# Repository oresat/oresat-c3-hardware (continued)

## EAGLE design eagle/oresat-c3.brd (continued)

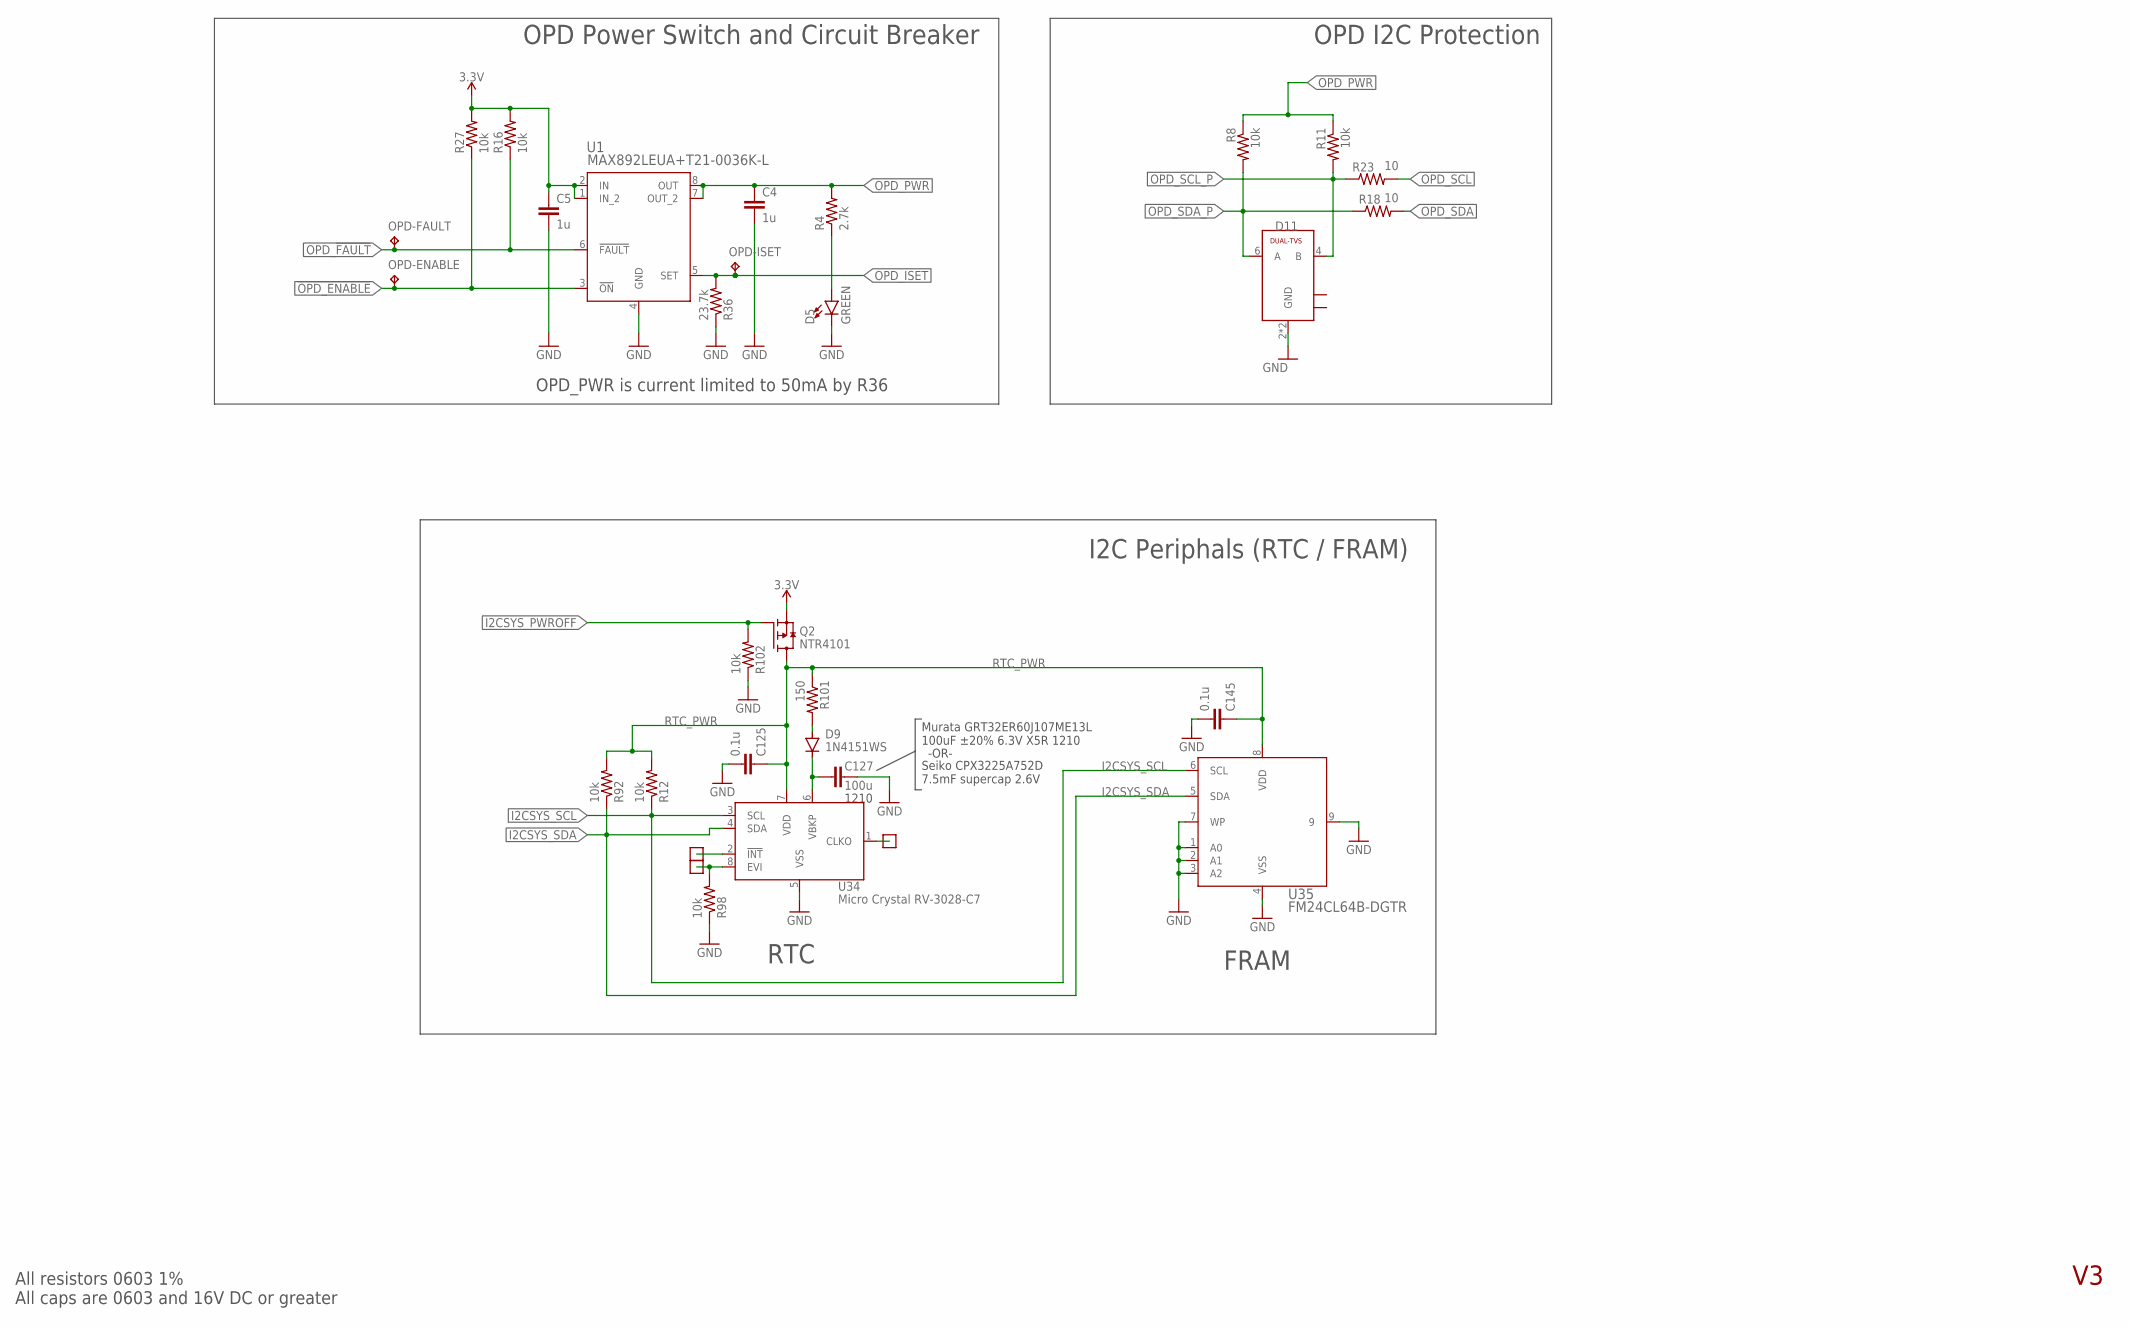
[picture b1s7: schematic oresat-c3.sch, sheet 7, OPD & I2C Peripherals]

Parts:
C4, C5: 1u; .0603-C-NOSILK
C125, C145: 0.1u; .0603-C-NOSILK
C127: 100u; C1210K
D5: GREEN; LED-0603; MANUFACTURER_PART_NUMBER 150060VS55040; DIGI-KEY_PART_NUMBER 732-12017-1-ND
D9: 1N4151WS; SOD323-R
D11: SN65220; SOT23-6; MANUFACTURER_PART_NUMBER SN65220DBVRG4
OPD-ENABLE: TEST-POINT-LARGE; 1X01
OPD-FAULT: TEST-POINT-LARGE; 1X01
OPD-ISET: TEST-POINT-LARGE; 1X01
Q2: NTR4101; SOT23-3
R4: 2.7k; .0603-C-NOSILK
R8, R11, R12, R16, R27, R92, R98, R102: 10k; .0603-C-NOSILK
R18, R23: 10; .0603-C-NOSILK
R36: 23.7k; .0603-C-NOSILK
R101: 150; .0603-C-NOSILK
TP16, TP23, TP24: TEST-POINT-LARGE-SQUARE; 1X01
U1: MAX892LEUA+T21-0036K-L; 21-0036K-L; MOUSER_PART_NUMBER 700-MAX892LEUAT
U34: Micro Crystal RV-3028-C7; RV3028C732768KHZ1PPMTAQC
U35: FM24CL64B-DGTR; TDFN-8

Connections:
3.3V: C5.1, Q2.2 (S), R16.2, R27.2, U1.1 (IN_2), U1.2 (IN); also elsewhere on the board
!OPD_ENABLE: OPD-ENABLE.1, R27.1, U1.3 (!ON); also elsewhere on the board
GND: C4.2, C5.2, C125.2, C127.2, C145.2, D5.C, D11.2 (GND), D11.5 (GND), R36.1, R98.1, R102.1, U1.4 (GND), U34.5 (VSS), U35.1 (A0), U35.2 (A1), U35.3 (A2), U35.4 (VSS), U35.7 (WP), U35.9; also elsewhere on the board
I2CSYS_PWROFF: Q2.1 (G), R102.2; also elsewhere on the board
I2CSYS_SCL: R12.1, U34.3 (SCL), U35.6 (SCL); also elsewhere on the board
I2CSYS_SDA: R92.1, U34.4 (SDA), U35.5 (SDA); also elsewhere on the board
unnamed: R98.2, TP23.1, U34.8 (EVI)
unnamed: TP16.1, U34.2 (!INT)
unnamed: TP24.1, U34.1 (CLKO)
unnamed: D9.A, R101.2
unnamed: C127.1, D9.C, U34.6 (VBKP)
unnamed: D5.A, R4.1
OPD_!FAULT: OPD-FAULT.1, R16.1, U1.6 (!FAULT); also elsewhere on the board
OPD_ISET: OPD-ISET.1, R36.2, U1.5 (SET); also elsewhere on the board
OPD_PWR: C4.1, R4.2, R8.1, R11.1, U1.7 (OUT_2), U1.8 (OUT); also elsewhere on the board
OPD_SCL: R23.2; also elsewhere on the board
OPD_SCL_P: D11.4 (B), R11.2, R23.1; also elsewhere on the board
OPD_SDA: R18.2; also elsewhere on the board
OPD_SDA_P: D11.6 (A), R8.2, R18.1; also elsewhere on the board
RTC_PWR: C125.1, C145.1, Q2.3 (D), R12.2, R92.2, R101.1, U34.7 (VDD), U35.8 (VDD)

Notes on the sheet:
All resistors 0603 1% All caps are 0603 and 16V DC or greater
OPD Power Switch and Circuit Breaker
OPD_PWR is current limited to 50mA by R36
1210
Murata GRT32ER60J107ME13L 100uF ±20% 6.3V X5R 1210
Seiko CPX3225A752D 7.5mF supercap 2.6V
-OR-
RTC
FRAM
I2C Periphals (RTC / FRAM)
OPD I2C Protection

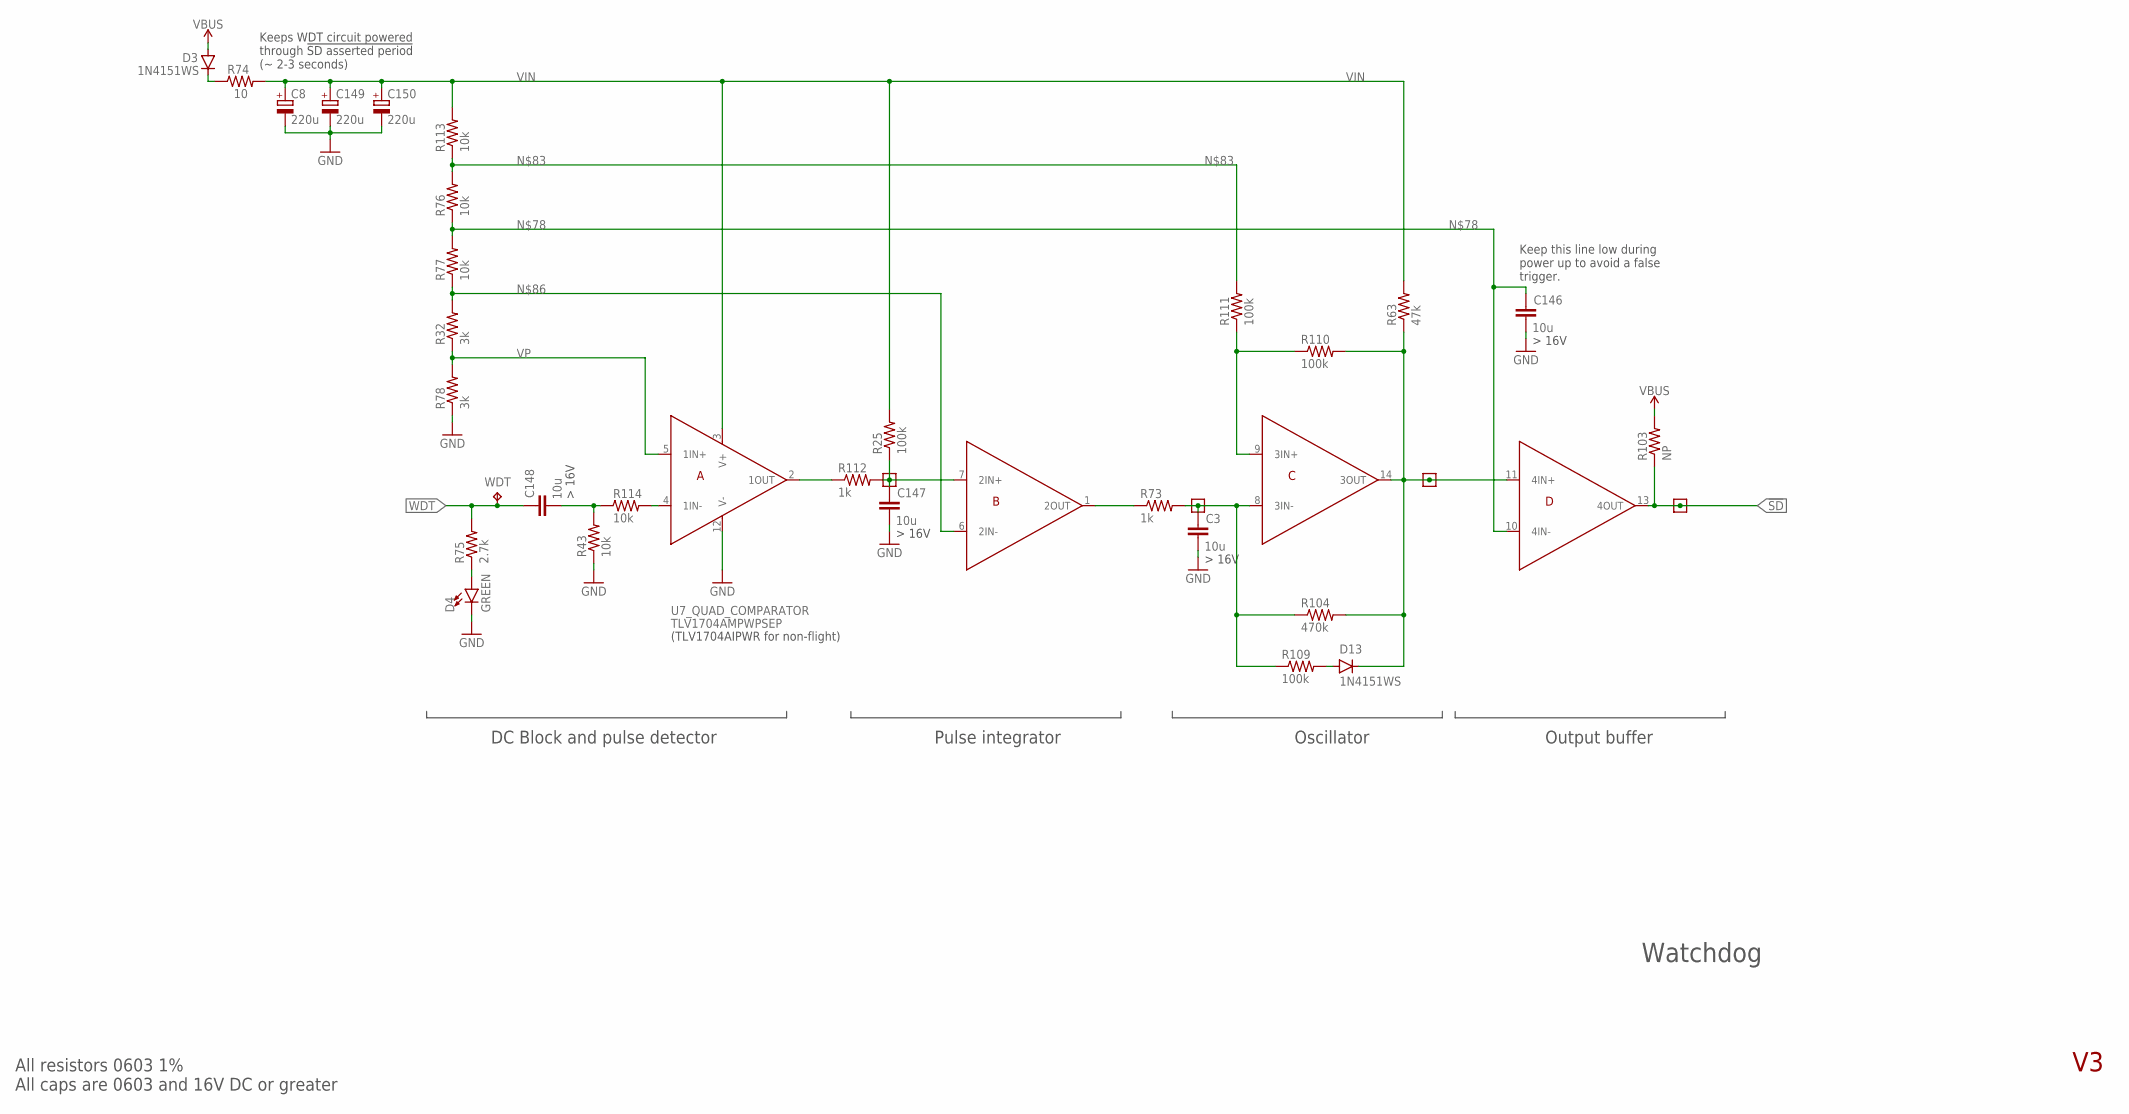
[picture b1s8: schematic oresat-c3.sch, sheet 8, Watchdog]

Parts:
C3, C146, C147, C148: 10u; .0603-C-NOSILK
C8, C149, C150: 220u; D/7343-31R
D3, D13: 1N4151WS; SOD323-R
D4: GREEN; LED-0603; MANUFACTURER_PART_NUMBER 150060VS55040; DIGI-KEY_PART_NUMBER 732-12017-1-ND
R25, R109, R110, R111: 100k; .0603-C-NOSILK
R32, R78: 3k; .0603-C-NOSILK
R43, R76, R77, R113, R114: 10k; .0603-C-NOSILK
R63: 47k; .0603-C-NOSILK
R73, R112: 1k; .0603-C-NOSILK
R74: 10; 1206-C
R75: 2.7k; .0603-C-NOSILK
R103: NP; .0603-C-NOSILK
R104: 470k; .0603-C-NOSILK
TP15, TP25, TP26, TP27: TEST-POINT-LARGE-SQUARE; 1X01
U7: TLV1704AMPWPSEP; SOP65P640X120-14N
WDT: TEST-POINT-LARGE; 1X01

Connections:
!SD: R103.1, TP15.1, U7.13 (4OUT); also elsewhere on the board
GND: C3.2, C8.-, C146.2, C147.2, C149.-, C150.-, D4.C, R43.1, R78.1, U7.12 (V-); also elsewhere on the board
unnamed: R110.1, R111.1, U7.9 (3IN+)
unnamed: D3.C, R74.1
unnamed: D4.A, R75.1
unnamed: D13.C, R63.1, R104.2, R110.2, TP25.1, U7.11 (4IN+), U7.14 (3OUT)
unnamed: R114.2, U7.4 (1IN-)
unnamed: D13.A, R109.2
unnamed: C146.1, R76.1, R77.2, U7.10 (4IN-)
unnamed: C148.2, R43.2, R114.1
unnamed: R73.1, U7.1 (2OUT)
unnamed: C147.1, R25.1, R112.2, TP27.1, U7.7 (2IN+)
unnamed: R76.2, R111.2, R113.1
unnamed: R112.1, U7.2 (1OUT)
unnamed: R32.2, R77.1, U7.6 (2IN-)
VBUS: D3.A, R103.2; also elsewhere on the board
VIN: C8.+, C149.+, C150.+, R25.2, R63.2, R74.2, R113.2, U7.3 (V+)
VP: R32.1, R78.2, U7.5 (1IN+)
VT: C3.1, R73.2, R104.1, R109.1, TP26.1, U7.8 (3IN-)
WDT: C148.1, R75.2, WDT.1; also elsewhere on the board

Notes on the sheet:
Watchdog
(TLV1704AIPWR for non-flight)
All resistors 0603 1% All caps are 0603 and 16V DC or greater
DC Block and pulse detector
Pulse integrator
Oscillator
Output buffer
Keep this line low during power up to avoid a false trigger.
Keeps WDT circuit powered through !SD asserted period (~ 2-3 seconds)

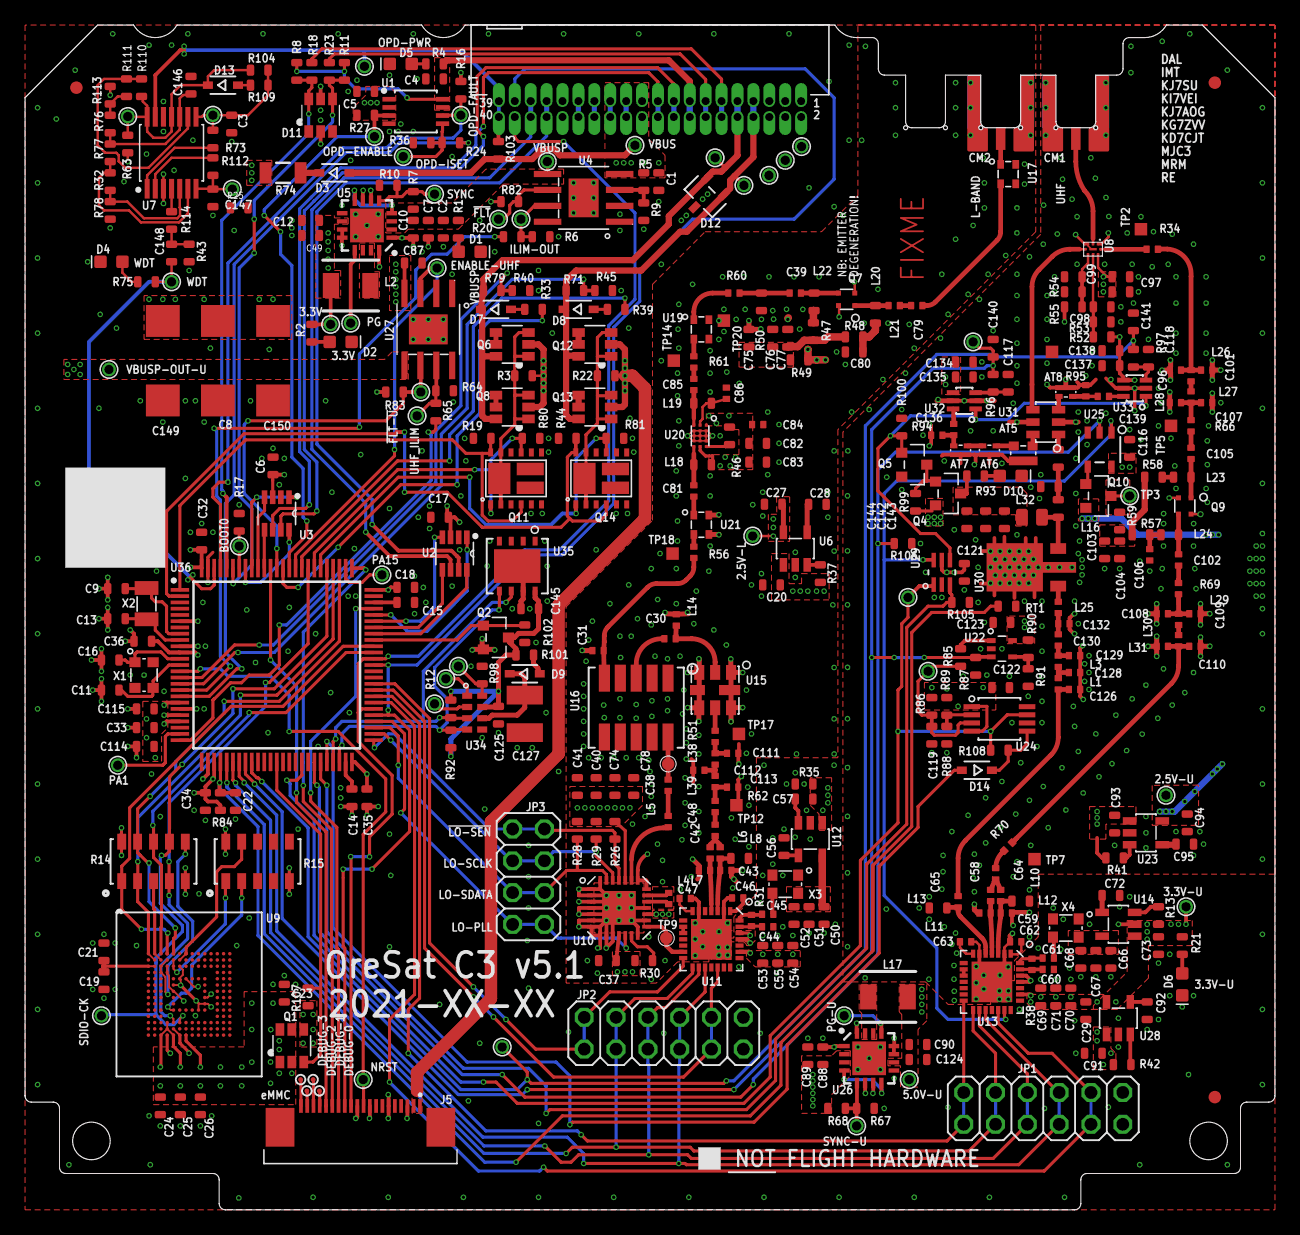
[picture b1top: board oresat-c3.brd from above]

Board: 4 copper layers, 99.8 x 94.6 mm, 441 parts (0 on the bottom side), 262 nets.

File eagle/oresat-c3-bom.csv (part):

"Part";"Value";"Device";"Package";"Description";"BOM";"DESCRIPTION";"DIGI-KEY_PART_NUMBER";"DIS";"DISTRIBUTOR";"DPN";"HEIGHT";"INVENTORY";"LABEL";"MANUFACTURER";"MANUFACTURER_NAME";"MANUFACTURER_PART_NUMBER";"MFR";"MOUSER_PART_#";"MOUSER_PART_NUMBER";"MOUSER_PRICE-STOCK";"MPN";"POPULARITY";"PROD_ID";"RS_PART_NUMBER";"RS_PRICE-STOCK";"SPICEPREFIX";"VALUE";"VDC";"VENDOR";
"!FLT";"TEST-POINT-LARGE";"TEST-POINT-LARGE";"1X01";"";"";"";"";"";"";"";"";"";"";"";"";"";"";"";"";"";"";"";"";"";"";"";"";"";"";
"!FLT-U";"TEST-POINT-LARGE";"TEST-POINT-LARGE";"1X01";"";"";"";"";"";"";"";"";"";"";"";"";"";"";"";"";"";"";"";"";"";"";"";"";"";"";
"2.5V-L";"TEST-POINT-LARGE";"TEST-POINT-LARGE";"1X01";"";"";"";"";"";"";"";"";"";"";"";"";"";"";"";"";"";"";"";"";"";"";"";"";"";"";
"2.5V-U";"TEST-POINT-LARGE";"TEST-POINT-LARGE";"1X01";"";"";"";"";"";"";"";"";"";"";"";"";"";"";"";"";"";"";"";"";"";"";"";"";"";"";
"3.3V";"TEST-POINT-LARGE";"TEST-POINT-LARGE";"1X01";"";"";"";"";"";"";"";"";"";"";"";"";"";"";"";"";"";"";"";"";"";"";"";"";"";"";
"3.3V-U";"TEST-POINT-LARGE";"TEST-POINT-LARGE";"1X01";"";"";"";"";"";"";"";"";"";"";"";"";"";"";"";"";"";"";"";"";"";"";"";"";"";"";
"5.0V-U";"TEST-POINT-LARGE";"TEST-POINT-LARGE";"1X01";"";"";"";"";"";"";"";"";"";"";"";"";"";"";"";"";"";"";"";"";"";"";"";"";"";"";
"BOOT0";"TEST-POINT-LARGE";"TEST-POINT-LARGE";"1X01";"";"EXCLUDE";"";"";"";"";"";"";"";"";"";"";"";"";"";"";"";"";"";"";"";"";"";"";"";"";
"C1";"1u";"CAP0603-1UF-25VDC";".0603-C-NOSILK-RESISTOR";"1µF ±10% 25V Ceramic Capacitor X5R 0603 (1608 Metric)";"";"1µF ±10% 25V Ceramic Capacitor X5R 0603 (1608 Metric)";"311-1445-1-ND";"";"";"";"";"";"";"YAGEO (PHYCOMP)";"";"CC0603KRX5R8BB105";"";"";"";"";"";"";"";"";"";"";"";"25V";"";
"C2";"0.1u";"CAP0603-0.1UF";".0603-B-NOSILK-CAP";"0.1µF ±10% 10V Ceramic Capacitor X5R 0603 (1608 Metric)";"";"0.1µF ±10% 10V Ceramic Capacitor X5R 0603 (1608 Metric)";"478-0603ZD104KAT2ACT-ND";"";"";"";"";"";"";"AVX";"";"0603ZD104KAT2A";"";"";"";"";"";"";"";"";"";"";"";"10V";"";
"C3";"0.1u";"CAP0603-0.1UF";".0603-B-NOSILK-CAP";"0.1µF ±10% 10V Ceramic Capacitor X5R 0603 (1608 Metric)";"";"0.1µF ±10% 10V Ceramic Capacitor X5R 0603 (1608 Metric)";"478-0603ZD104KAT2ACT-ND";"";"";"";"";"";"";"AVX";"";"0603ZD104KAT2A";"";"";"";"";"";"";"";"";"";"";"";"10V";"";
"C4";"1u";"CAP0603-1UF-25VDC";".0603-C-NOSILK-RESISTOR";"1µF ±10% 25V Ceramic Capacitor X5R 0603 (1608 Metric)";"";"1µF ±10% 25V Ceramic Capacitor X5R 0603 (1608 Metric)";"311-1445-1-ND";"";"";"";"";"";"";"YAGEO (PHYCOMP)";"";"CC0603KRX5R8BB105";"";"";"";"";"";"";"";"";"";"";"";"25V";"";
"C5";"1u";"CAP0603-1UF-25VDC";".0603-C-NOSILK-RESISTOR";"1µF ±10% 25V Ceramic Capacitor X5R 0603 (1608 Metric)";"";"1µF ±10% 25V Ceramic Capacitor X5R 0603 (1608 Metric)";"311-1445-1-ND";"";"";"";"";"";"";"YAGEO (PHYCOMP)";"";"CC0603KRX5R8BB105";"";"";"";"";"";"";"";"";"";"";"";"25V";"";
"C6";"0.1u";"CAP0603-0.1UF";".0603-B-NOSILK-CAP";"0.1µF ±10% 10V Ceramic Capacitor X5R 0603 (1608 Metric)";"";"0.1µF ±10% 10V Ceramic Capacitor X5R 0603 (1608 Metric)";"478-0603ZD104KAT2ACT-ND";"";"";"";"";"";"";"AVX";"";"0603ZD104KAT2A";"";"";"";"";"";"";"";"";"";"";"";"10V";"";
"C7";"10u";"CAP0603-10UF-25VDC";".0603-B-NOSILK-CAP";"10µF ±10% 25V Ceramic Capacitor X5R 0603 (1608 Metric)";"";"10µF ±10% 25V Ceramic Capacitor X5R 0603 (1608 Metric)";"490-18214-1-ND";"";"";"";"";"";"";"Murata Electronics";"";"GRM188R61E106KA73D";"";"";"";"";"";"";"";"";"";"";"";"25V";"";
"C8";"0.1u";"CAP0603-0.1UF";".0603-B-NOSILK-CAP";"0.1µF ±10% 10V Ceramic Capacitor X5R 0603 (1608 Metric)";"";"0.1µF ±10% 10V Ceramic Capacitor X5R 0603 (1608 Metric)";"478-0603ZD104KAT2ACT-ND";"";"";"";"";"";"";"AVX";"";"0603ZD104KAT2A";"";"";"";"";"";"";"";"";"";"";"";"10V";"";
"C9";"0.1u";"CAP0603-0.1UF";".0603-B-NOSILK-CAP";"0.1µF ±10% 10V Ceramic Capacitor X5R 0603 (1608 Metric)";"";"0.1µF ±10% 10V Ceramic Capacitor X5R 0603 (1608 Metric)";"478-0603ZD104KAT2ACT-ND";"";"";"";"";"";"";"AVX";"";"0603ZD104KAT2A";"";"";"";"";"";"";"";"";"";"";"";"10V";"";
"C10";"1u";"CAP0603-1UF-25VDC";".0603-C-NOSILK-RESISTOR";"1µF ±10% 25V Ceramic Capacitor X5R 0603 (1608 Metric)";"";"1µF ±10% 25V Ceramic Capacitor X5R 0603 (1608 Metric)";"311-1445-1-ND";"";"";"";"";"";"";"YAGEO (PHYCOMP)";"";"CC0603KRX5R8BB105";"";"";"";"";"";"";"";"";"";"";"";"25V";"";
"C11";"20p";"CAP0603-20PF";".0603-B-NOSILK-CAP";"20pF ±5% 50V Ceramic Capacitor C0G, NP0 0603 (1608 Metric)";"";"20pF ±5% 50V Ceramic Capacitor C0G, NP0 0603 (1608 Metric)";"GRM1885C1H200JA01J-ND";"";"";"";"";"";"";"Murata Electronics";"";"GRM1885C1H200JA01J";"";"";"";"";"";"";"";"";"";"";"";"50V";"";
"C12";"22u";"CAP0603-22UF";".0603-B-NOSILK-CAP";"22µF ±20% 10V Ceramic Capacitor X5R 0603 (1608 Metric)";"";"22µF ±20% 10V Ceramic Capacitor X5R 0603 (1608 Metric)";"ZRB18AR61A226ME01L-ND";"";"";"";"";"";"";"Murata Electronics";"";"ZRB18AR61A226ME01L";"";"";"";"";"";"";"";"";"";"";"";"10V";"";
"C13";"0.1u";"CAP0603-0.1UF";".0603-B-NOSILK-CAP";"0.1µF ±10% 10V Ceramic Capacitor X5R 0603 (1608 Metric)";"";"0.1µF ±10% 10V Ceramic Capacitor X5R 0603 (1608 Metric)";"478-0603ZD104KAT2ACT-ND";"";"";"";"";"";"";"AVX";"";"0603ZD104KAT2A";"";"";"";"";"";"";"";"";"";"";"";"10V";"";
"C14";"2.2u";"CAP0603-2.2UF";".0603-B-NOSILK-CAP";"2.2µF ±20% 10V Ceramic Capacitor X7R 0603 (1608 Metric)";"";"2.2µF ±20% 10V Ceramic Capacitor X7R 0603 (1608 Metric)";"445-5959-1-ND";"";"";"";"";"";"";"TDK";"";"C1608X7R1A225M080AC";"";"";"";"";"";"";"";"";"";"";"";"10V";"";
"C16";"20p";"CAP0603-20PF";".0603-B-NOSILK-CAP";"20pF ±5% 50V Ceramic Capacitor C0G, NP0 0603 (1608 Metric)";"";"20pF ±5% 50V Ceramic Capacitor C0G, NP0 0603 (1608 Metric)";"GRM1885C1H200JA01J-ND";"";"";"";"";"";"";"Murata Electronics";"";"GRM1885C1H200JA01J";"";"";"";"";"";"";"";"";"";"";"";"50V";"";
"C17";"0.1u";"CAP0603-0.1UF";".0603-B-NOSILK-CAP";"0.1µF ±10% 10V Ceramic Capacitor X5R 0603 (1608 Metric)";"";"0.1µF ±10% 10V Ceramic Capacitor X5R 0603 (1608 Metric)";"478-0603ZD104KAT2ACT-ND";"";"";"";"";"";"";"AVX";"";"0603ZD104KAT2A";"";"";"";"";"";"";"";"";"";"";"";"10V";"";
"C19";"2.2u";"CAP0603-2.2UF";".0603-B-NOSILK-CAP";"2.2µF ±20% 10V Ceramic Capacitor X7R 0603 (1608 Metric)";"";"2.2µF ±20% 10V Ceramic Capacitor X7R 0603 (1608 Metric)";"445-5959-1-ND";"";"";"";"";"";"";"TDK";"";"C1608X7R1A225M080AC";"";"";"";"";"";"";"";"";"";"";"";"10V";"";
"C20";"1u";"CAP0603-1UF-25VDC";".0603-C-NOSILK-RESISTOR";"1µF ±10% 25V Ceramic Capacitor X5R 0603 (1608 Metric)";"";"1µF ±10% 25V Ceramic Capacitor X5R 0603 (1608 Metric)";"311-1445-1-ND";"";"";"";"";"";"";"YAGEO (PHYCOMP)";"";"CC0603KRX5R8BB105";"";"";"";"";"";"";"";"";"";"";"";"25V";"";
"C21";"0.1u";"CAP0603-0.1UF";".0603-B-NOSILK-CAP";"0.1µF ±10% 10V Ceramic Capacitor X5R 0603 (1608 Metric)";"";"0.1µF ±10% 10V Ceramic Capacitor X5R 0603 (1608 Metric)";"478-0603ZD104KAT2ACT-ND";"";"";"";"";"";"";"AVX";"";"0603ZD104KAT2A";"";"";"";"";"";"";"";"";"";"";"";"10V";"";
"C22";"0.1u";"CAP0603-0.1UF";".0603-B-NOSILK-CAP";"0.1µF ±10% 10V Ceramic Capacitor X5R 0603 (1608 Metric)";"";"0.1µF ±10% 10V Ceramic Capacitor X5R 0603 (1608 Metric)";"478-0603ZD104KAT2ACT-ND";"";"";"";"";"";"";"AVX";"";"0603ZD104KAT2A";"";"";"";"";"";"";"";"";"";"";"";"10V";"";
"C23";"1u";"CAP0603-1UF-25VDC";".0603-C-NOSILK-RESISTOR";"1µF ±10% 25V Ceramic Capacitor X5R 0603 (1608 Metric)";"";"1µF ±10% 25V Ceramic Capacitor X5R 0603 (1608 Metric)";"311-1445-1-ND";"";"";"";"";"";"";"YAGEO (PHYCOMP)";"";"CC0603KRX5R8BB105";"";"";"";"";"";"";"";"";"";"";"";"25V";"";
"C24";"1u";"CAP0603-1UF-25VDC";".0603-C-NOSILK-RESISTOR";"1µF ±10% 25V Ceramic Capacitor X5R 0603 (1608 Metric)";"";"1µF ±10% 25V Ceramic Capacitor X5R 0603 (1608 Metric)";"311-1445-1-ND";"";"";"";"";"";"";"YAGEO (PHYCOMP)";"";"CC0603KRX5R8BB105";"";"";"";"";"";"";"";"";"";"";"";"25V";"";
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
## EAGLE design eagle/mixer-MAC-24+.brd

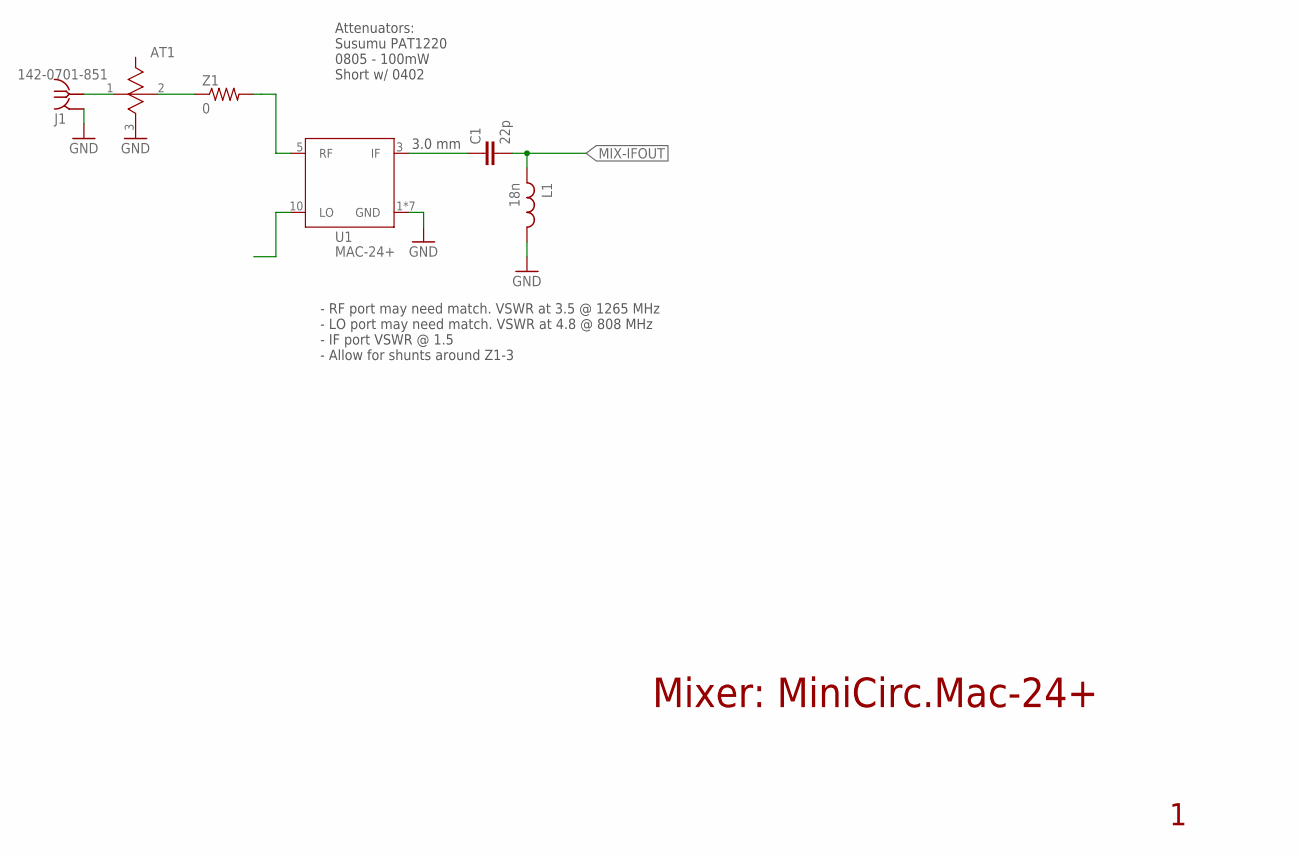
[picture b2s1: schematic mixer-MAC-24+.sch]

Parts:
AT1: PAT1220; 0805
C1: 22p; .0402-B-NOSILK
J1: 142-0701-851
L1: 18n; .0402-B-NOSILK
U1: MAC-24+
Z1: 0; .0402-C-NOSILK

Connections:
GND: AT1.3 (GND), J1.GND1 (GND), J1.GND2 (GND), J1.GND3 (GND), J1.GND4 (GND), L1.2, U1.1 (GND), U1.2 (GND), U1.4 (GND), U1.6 (GND), U1.7 (GND), U1.8 (GND), U1.9 (GND)
MIX-IFOUT: C1.2, L1.1
unnamed: C1.1, U1.3 (IF)
unnamed: U1.5 (RF), Z1.2
unnamed: AT1.2, Z1.1
RF: AT1.1, J1.RF1 (RF)

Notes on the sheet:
Mixer: MiniCirc.Mac-24+
- RF port may need match. VSWR at 3.5 @ 1265 MHz - LO port may need match. VSWR at 4.8 @ 808 MHz - IF port VSWR @ 1.5 - Allow for shunts around Z1-3
Attenuators: Susumu PAT1220 0805 - 100mW Short w/ 0402
3.0 mm

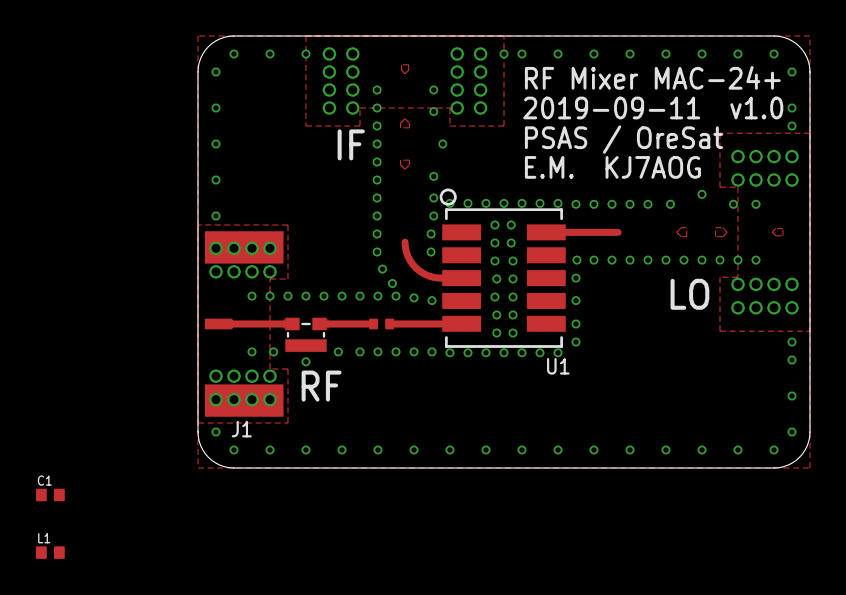
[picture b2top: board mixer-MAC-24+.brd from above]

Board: 4 copper layers, 34.0 x 24.0 mm, 6 parts (0 on the bottom side), 6 nets.

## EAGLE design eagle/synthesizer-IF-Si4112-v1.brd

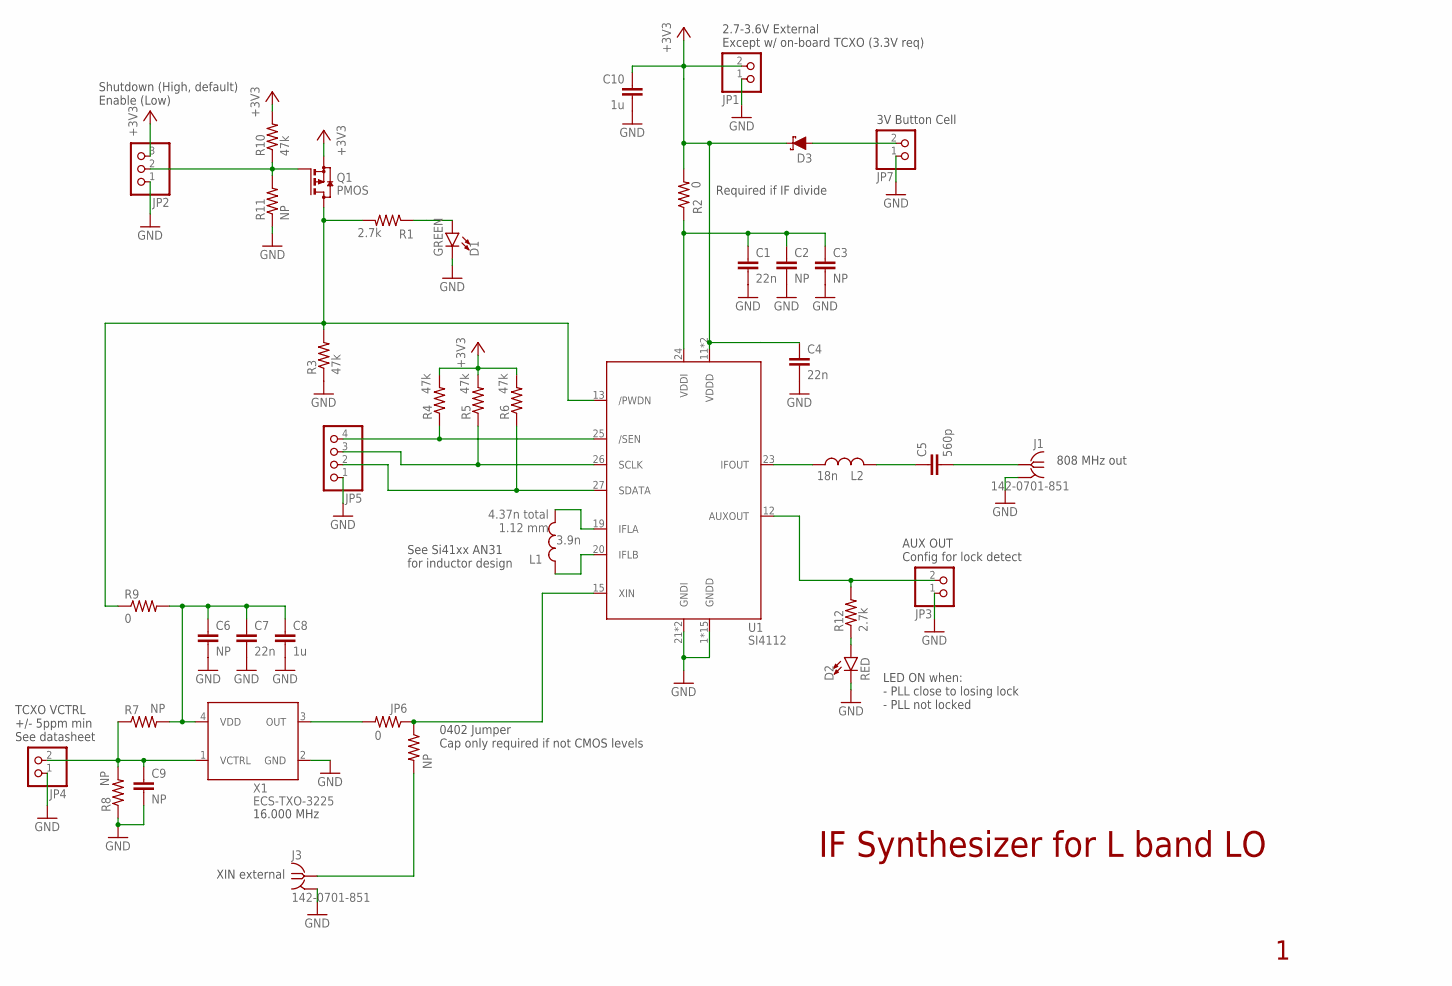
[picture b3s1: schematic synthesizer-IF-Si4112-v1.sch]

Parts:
C1, C4, C7: 22n; .0603-B-NOSILK
C2, C3, C6, C9: NP; .0603-B-NOSILK
C5: 560p; .0402-B-NOSILK
C8, C10: 1u; .0603-B-NOSILK
D1: GREEN; LED-0603
D2: RED; LED-0603
D3: 120mA/40V/370mV; SOD-523
J1, J3: 142-0701-851
JP1, JP3, JP4, JP7: PINHD-1X2; 1X02
JP2: PINHD-1X3; 1X03
JP5: PINHD-1X4; 1X04
JP6: 0; .0402-B-NOSILK
L1: 3.9n; .0402-C-NOSILK
L2: 18n; .0402-B-NOSILK
Q1: PMOS; SOT23
R1, R12: 2.7k; .0603-B-NOSILK
R2, R9: 0; .0603-B-NOSILK
R3, R4, R5, R6, R10: 47k; .0402-B-NOSILK
R7, R8: NP; .0603-B-NOSILK
R11, R99: NP; .0402-B-NOSILK
U1: SI4112; QFN28-5X5-WITH-CENTER-PAD
X1: ECS-TXO-3225; 3.2X2.5

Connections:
+3V3: C4.1, C10.1, D3.C, JP1.2, JP2.3, Q1.2 (S), R2.2, R4.2, R5.2, R6.2, R10.2, U1.11 (VDDD), U1.17 (VDDD)
/SEN: JP5.4, R4.1, U1.25 (/SEN)
AUX: JP3.2, R12.2, U1.12 (AUXOUT)
GND: C1.2, C2.2, C3.2, C4.2, C6.2, C7.2, C8.2, C9.2, C10.2, D1.C, D2.C, J1.GND1 (GND), J1.GND2 (GND), J1.GND3 (GND), J1.GND4 (GND), J3.GND1 (GND), J3.GND2 (GND), J3.GND3 (GND), J3.GND4 (GND), JP1.1, JP2.1, JP3.1, JP4.1, JP5.1, JP7.1, R3.1, R8.1, R11.1, U1.1 (GNDD), U1.2 (GNDD), U1.3 (GNDD), U1.4 (GNDD), U1.5 (GNDD), U1.6 (GNDD), U1.7 (GNDD), U1.8 (GNDD), U1.9 (GNDD), U1.10 (GNDD), U1.14 (GNDD), U1.16 (GNDD), U1.18 (GNDD), U1.21 (GNDI), U1.22 (GNDI), U1.28 (GNDD), U1.PAD (GNDD), X1.2 (GND)
IF_OUT: C5.2, J1.RF1 (RF)
unnamed: D3.A, JP7.2
unnamed: L1.2, U1.19 (IFLA)
unnamed: L1.1, U1.20 (IFLB)
unnamed: JP2.2, Q1.1 (G), R10.1, R11.2
unnamed: Q1.3 (D), R1.2, R3.2, R9.1, U1.13 (/PWDN)
unnamed: JP6.2, X1.3 (OUT)
unnamed: C6.1, C7.1, C8.1, R7.2, R9.2, X1.4 (VDD)
unnamed: C5.1, L2.2
unnamed: D1.A, R1.1
unnamed: D2.A, R12.1
unnamed: L2.1, U1.23 (IFOUT)
unnamed: C1.1, C2.1, C3.1, R2.1, U1.24 (VDDI)
REF_IN: J3.RF1 (RF), R99.2
SCLK: JP5.3, R5.1, U1.26 (SCLK)
SDATA: JP5.2, R6.1, U1.27 (SDATA)
VCTRL: C9.1, JP4.2, R7.1, R8.2, X1.1 (VCTRL)
XIN: JP6.1, R99.1, U1.15 (XIN)

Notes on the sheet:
IF Synthesizer for L band LO
4.37n total 1.12 mm
Required if IF divide
808 MHz out
XIN external
2.7-3.6V External Except w/ on-board TCXO (3.3V req)
16.000 MHz
0402 Jumper Cap only required if not CMOS levels
Shutdown (High, default) Enable (Low)
TCXO VCTRL +/- 5ppm min See datasheet
AUX OUT Config for lock detect
LED ON when: - PLL close to losing lock - PLL not locked
3V Button Cell
See Si41xx AN31 for inductor design

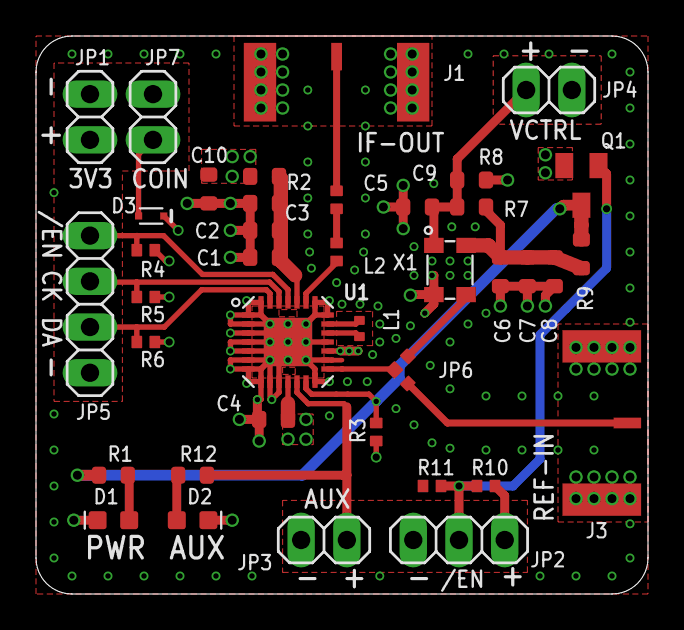
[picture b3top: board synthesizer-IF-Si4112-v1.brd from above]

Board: 4 copper layers, 34.0 x 31.0 mm, 40 parts (0 on the bottom side), 22 nets.

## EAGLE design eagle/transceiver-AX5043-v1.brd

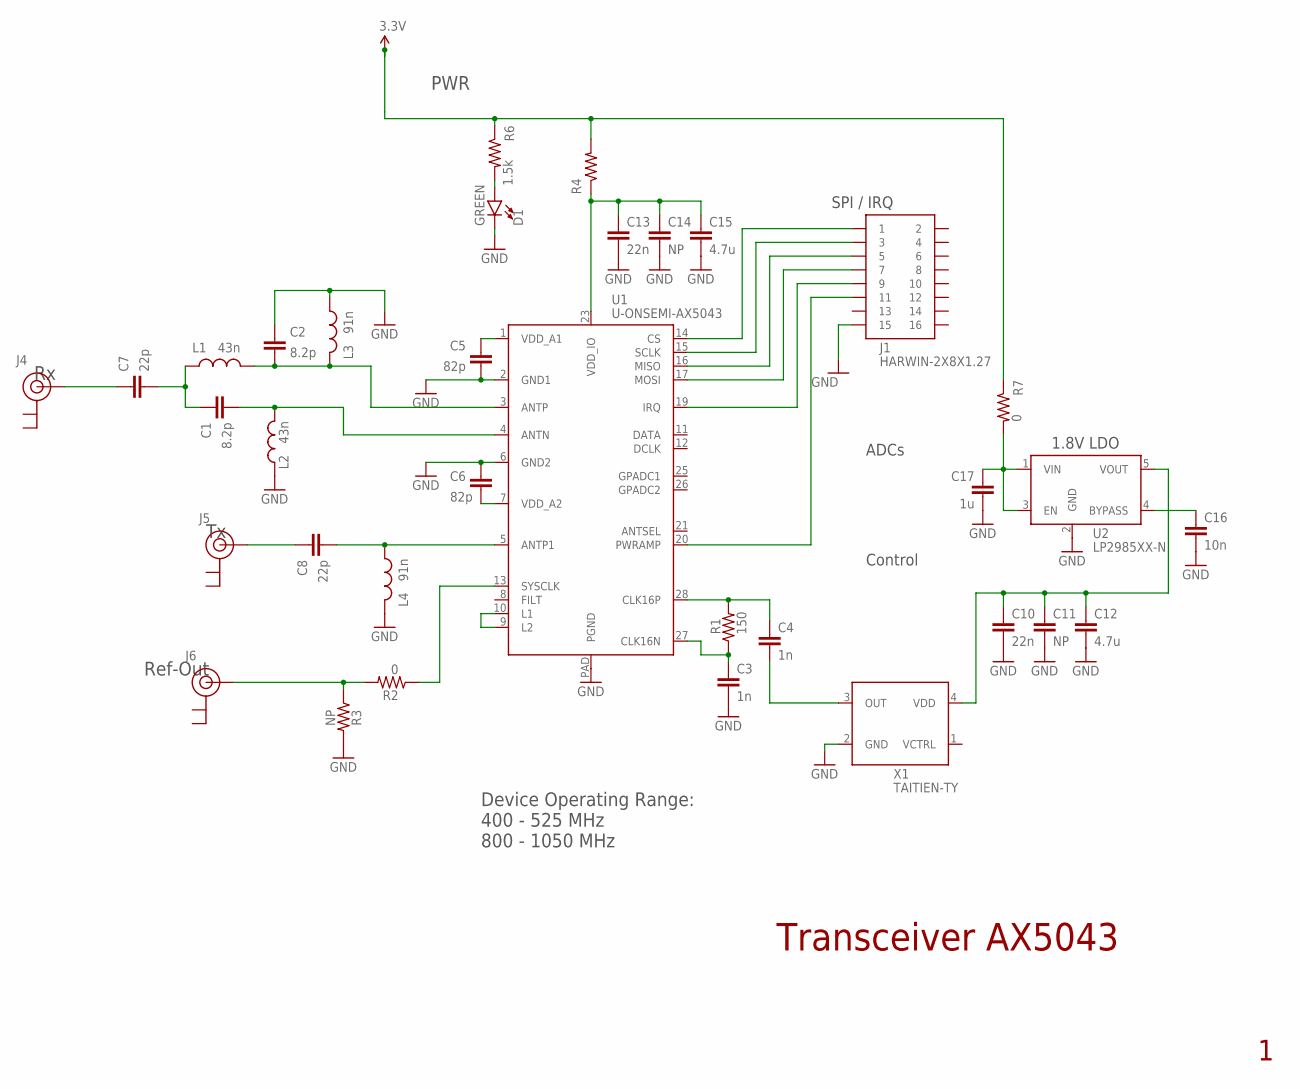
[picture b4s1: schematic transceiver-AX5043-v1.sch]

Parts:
C1, C2: 8.2p; .0402-C-NOSILK
C3, C4: 1n; .0402-C-NOSILK
C5, C6: 82p; .0402-C-NOSILK
C7, C8: 22p; .0402-C-NOSILK
C10, C13: 22n; .0603-C-NOSILK
C11, C14: NP; .0603-C-NOSILK
C12, C15: 4.7u; .0603-C-NOSILK
C16: 10n; .0603-C-NOSILK
C17: 1u; .0603-C-NOSILK
D1: GREEN; LED-0603
J1: HARWIN-2X8X1.27; 2X8X1.27
J4, J5, J6: U.FL
L1, L2: 43n; .0402-C-NOSILK
L3, L4: 91n; .0603-C-NOSILK
R1: 150; .0402-C-NOSILK
R2: 0; .0402-C-NOSILK
R3: NP; .0402-C-NOSILK
R4, R7: 0; .0603-C-NOSILK
R6: 1.5k; .0603-B-NOSILK
U1: U-ONSEMI-AX5043; QFN28-5X5-WITH-CENTER-PAD
U2: LP2985XX-N; SOT-23
X1: TAITIEN-TY; 2.5X2.0

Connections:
1V8: C10.1, C11.1, C12.1, U2.5 (VOUT), X1.4 (VDD)
3.3V: C13.1, C14.1, C15.1, C17.1, R4.1, R4.2, R6.1, R7.1, R7.2, U1.23 (VDD_IO), U2.1 (VIN), U2.3 (EN)
ANTN: C1.2, L2.2, U1.4 (ANTN)
ANTP: C2.2, L1.2, L3.1, U1.3 (ANTP)
ANTP1: C8.2, L4.2, U1.5 (ANTP1)
CLKN: C3.1, R1.1, U1.27 (CLK16N)
CLKP: C4.1, R1.2, U1.28 (CLK16P)
CS: J1.1, U1.14 (CS)
GND: C2.1, C3.2, C5.2, C6.1, C10.2, C11.2, C12.2, C13.2, C14.2, C15.2, C16.2, C17.2, D1.C, J1.15, L2.1, L3.2, L4.1, R3.2, U1.2 (GND1), U1.6 (GND2), U1.PAD (PGND), U2.2 (GND), X1.2 (GND)
IRQ: J1.9, U1.19 (IRQ)
LEDPWR: D1.A, R6.2
MISO: J1.5, U1.16 (MISO)
MOSI: J1.7, U1.17 (MOSI)
unnamed: C5.1, U1.1 (VDD_A1)
unnamed: U1.9 (L2), U1.10 (L1)
unnamed: C4.2, X1.3 (OUT)
unnamed: C1.1, C7.2, L1.1
unnamed: C16.1, U2.4 (BYPASS)
unnamed: C6.2, U1.7 (VDD_A2)
PWRAMP: J1.11, U1.20 (PWRAMP)
REF-OUT: J6.FEED (SIGNAL), R2.2, R3.1
RX: C7.1, J4.FEED (SIGNAL)
SCLK: J1.3, U1.15 (SCLK)
SYSCLK: R2.1, U1.13 (SYSCLK)
TX: C8.1, J5.FEED (SIGNAL)

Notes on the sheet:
Transceiver AX5043
Ref-Out
PWR
SPI / IRQ
Control
1.8V LDO
ADCs
Device Operating Range: 400 - 525 MHz 800 - 1050 MHz

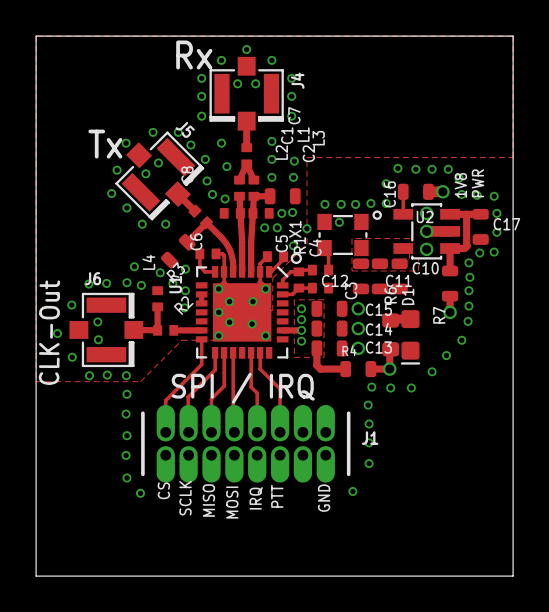
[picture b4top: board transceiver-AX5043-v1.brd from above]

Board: 4 copper layers, 26.5 x 30.0 mm, 34 parts (0 on the bottom side), 25 nets.
